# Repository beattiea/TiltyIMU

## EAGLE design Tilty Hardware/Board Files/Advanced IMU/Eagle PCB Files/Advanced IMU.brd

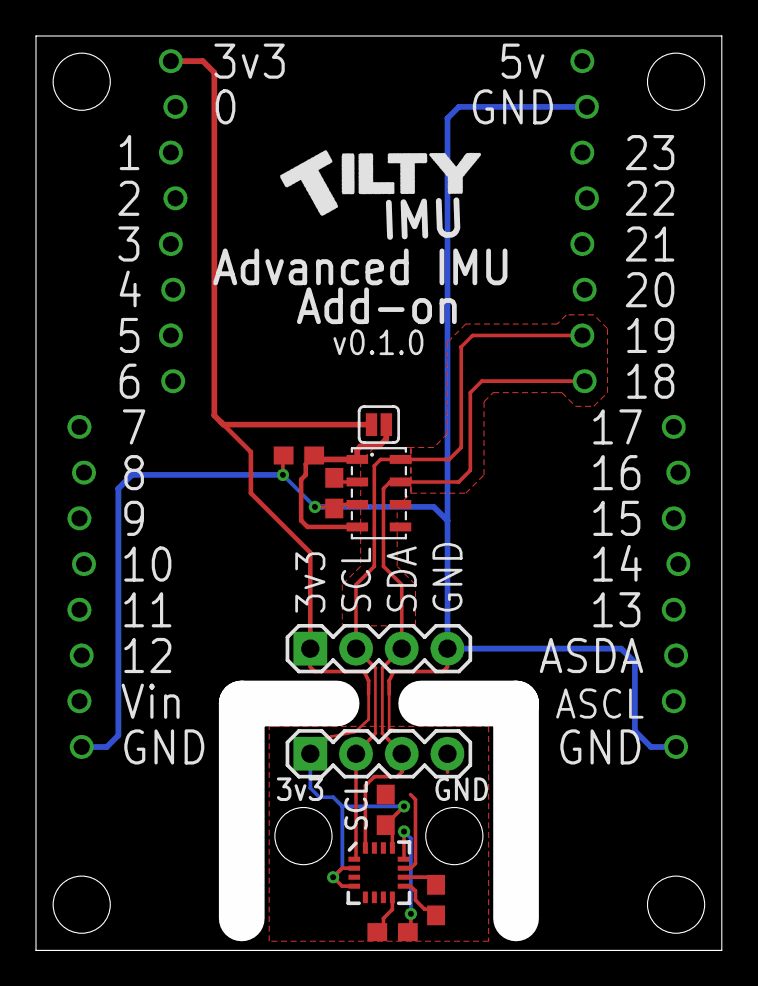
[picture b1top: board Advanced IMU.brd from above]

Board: 2 copper layers, 38.1 x 50.8 mm, 14 parts (0 on the bottom side), 9 nets.

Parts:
C6, C10, C12: 0.1uF; C0603
C7: 0.22uF; C0603
C8: 4.7uF; C0603
JP1, JP2, JP3, JP4: 8-PIN_HEADER; 8-PIN_RECEPTACLE_LOCK_NO-SS
JP5, JP6: 1X04
SJ1: SOLDERJUMPERNC; SJ_2S
U3: MPL3115A2LGA8; LGA8
U6: HMC5883LSMD; 16LPCC

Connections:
3V_SCL: JP4.P$7, JP5.2, JP6.2, U3.8, U6.1
3V_SDA: JP4.P$8, JP5.3, JP6.3, U3.7, U6.16
+3V3: C6.1, JP1.P$1, JP5.1, JP6.1, SJ1.2, U6.2, U6.4, U6.13
GND: C6.2, C8.2, C10.2, C12.1, JP2.P$8, JP3.P$8, JP4.P$2, JP5.4, JP6.4, U3.3, U6.9, U6.11
unnamed: C7.1, U6.8
unnamed: C7.2, U6.12
unnamed: C12.2, SJ1.1, U3.1, U3.4
unnamed: C8.1, U6.10
unnamed: C10.1, U3.2

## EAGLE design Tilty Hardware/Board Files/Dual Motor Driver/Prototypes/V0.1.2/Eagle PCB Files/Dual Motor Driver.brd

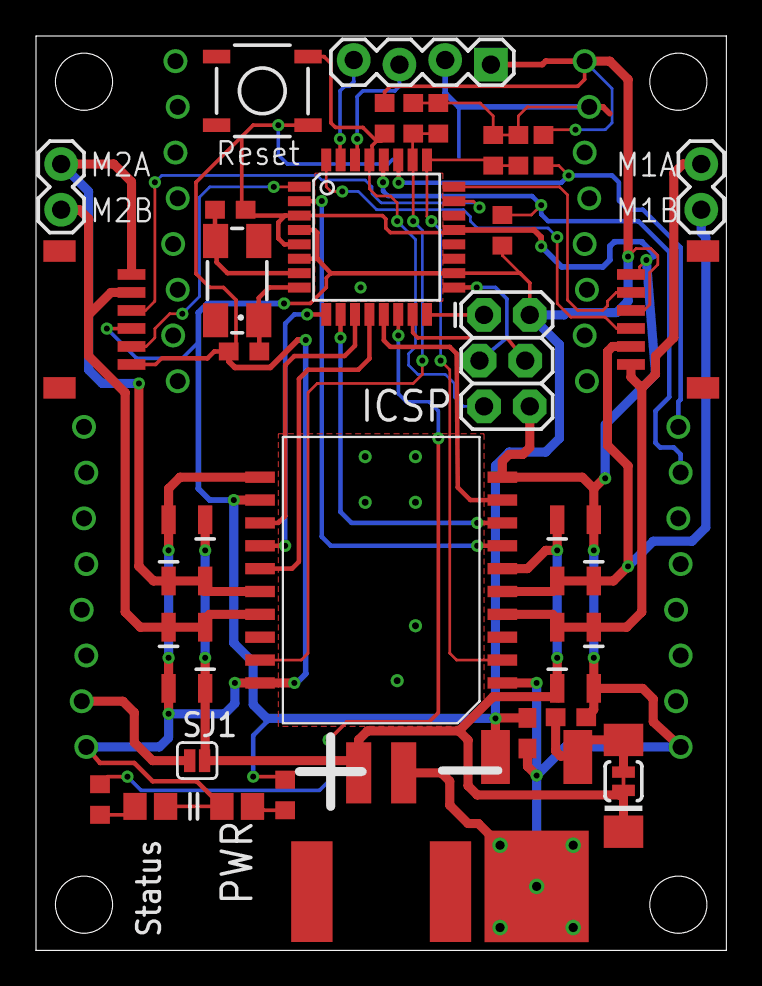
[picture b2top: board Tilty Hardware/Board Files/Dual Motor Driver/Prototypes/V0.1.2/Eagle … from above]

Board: 2 copper layers, 38.4 x 50.8 mm, 42 parts (0 on the bottom side), 34 nets.

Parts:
C2, C8: 22pF; C0603
C6: 4.7uF; C0603
C7: 0.1uF; C0603
D1, D2, D3, D4, D5, D6, D7, D8: SOD123
D9: DO214AA
D10, D11: LED-0805
J1: AVR_SPI_PRG_62X3_LOCK; 2X3_LOCK
JP1, JP2, JP3, JP4: 8-PIN_HEADER; 8-PIN_RECEPTACLE_LOCK_NO-SS
JP5, JP6: 6PIN-SH_RIGHT_ANGLE; 6PIN-SH_SERIES_RA
JP7: 2-POS_SMD_TERM_BLOCK; 2-POS_SMD_TERMINAL_BLOCK
JP8: 1X04_LOCK
JP9, JP10: 1X02
Q1: 16MHz; CTS406
R1: 10K; R0603
R2, R3, R4, R5: 1; R0603
R6, R7, R8, R9: R0603
S1: SWITCH-MOMENTARY-2SMD; TACTILE_SWITCH_SMD
SJ1: SOLDERJUMPERNC; SJ_2S
SJ2: SJ_2S-TRACE
U1: ATMEGA328P; TQFP32-08
U2: L298_BRIDGE_DRIVER; POWERSO20
U3: LM2931; TO263

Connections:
+5V: C6.1, J1.2, JP4.P$1, JP5.P$4, JP6.P$4, JP8.1, R1.2, R6.1, R7.2, R8.2, U1.4, U1.6, U1.18, U2.12, U3.P$3
+24V: D5.1, D6.1, D7.1, D8.1, D9.C, JP7.P$3, SJ1.2, SJ2.2, U2.6
ENC1A: JP6.P$3, U1.32
ENC1B: JP6.P$5, U1.24
ENC2A: JP5.P$3, U1.23
ENC2B: JP5.P$5, U1.1
GND: C2.1, C6.2, C7.2, C8.1, D1.2, D2.2, D3.2, D4.2, D10.2, D11.2, J1.6, JP2.P$1, JP3.P$1, JP4.P$2, JP5.P$6, JP6.P$6, JP7.P$4, JP8.2, R2.1, R3.1, R4.1, R5.1, S1.1, U1.3, U1.5, U1.21, U2.1, U2.10, U2.11, U2.20, U3.P$1
M1+: U1.2, U2.7
M1-: U1.13, U2.9
M1A: D1.1, D8.2, JP6.P$1, JP9.2, U2.4
M1B: D2.1, D7.2, JP6.P$2, JP9.1, U2.5
M2+: U1.11, U2.13
M2-: U1.12, U2.15
M2A: D3.1, D6.2, JP5.P$1, JP10.2, U2.16
M2B: D4.1, D5.2, JP5.P$2, JP10.1, U2.17
MISO: J1.1, U1.16
MOSI: J1.4, U1.15
unnamed: D10.1, R6.2
unnamed: D11.1, R9.2
unnamed: C7.1, D9.A, SJ2.1, U3.P$2
unnamed: R9.1, U1.14
unnamed: JP2.P$2, SJ1.1
unnamed: C8.2, Q1.3, U1.7
unnamed: C2.2, Q1.1, U1.8
PWM1: U1.10, U2.8
PWM2: U1.9, U2.14
RESET: J1.5, R1.1, S1.3, U1.29
RX: JP8.3, U1.30
SCK: J1.3, U1.17
SCL: JP3.P$7, R8.1, U1.28
SDA: JP3.P$8, R7.1, U1.27
SENSE_1: R2.2, R3.2, U1.25, U2.2
SENSE_2: R4.2, R5.2, U1.26, U2.19
TX: JP8.4, U1.31

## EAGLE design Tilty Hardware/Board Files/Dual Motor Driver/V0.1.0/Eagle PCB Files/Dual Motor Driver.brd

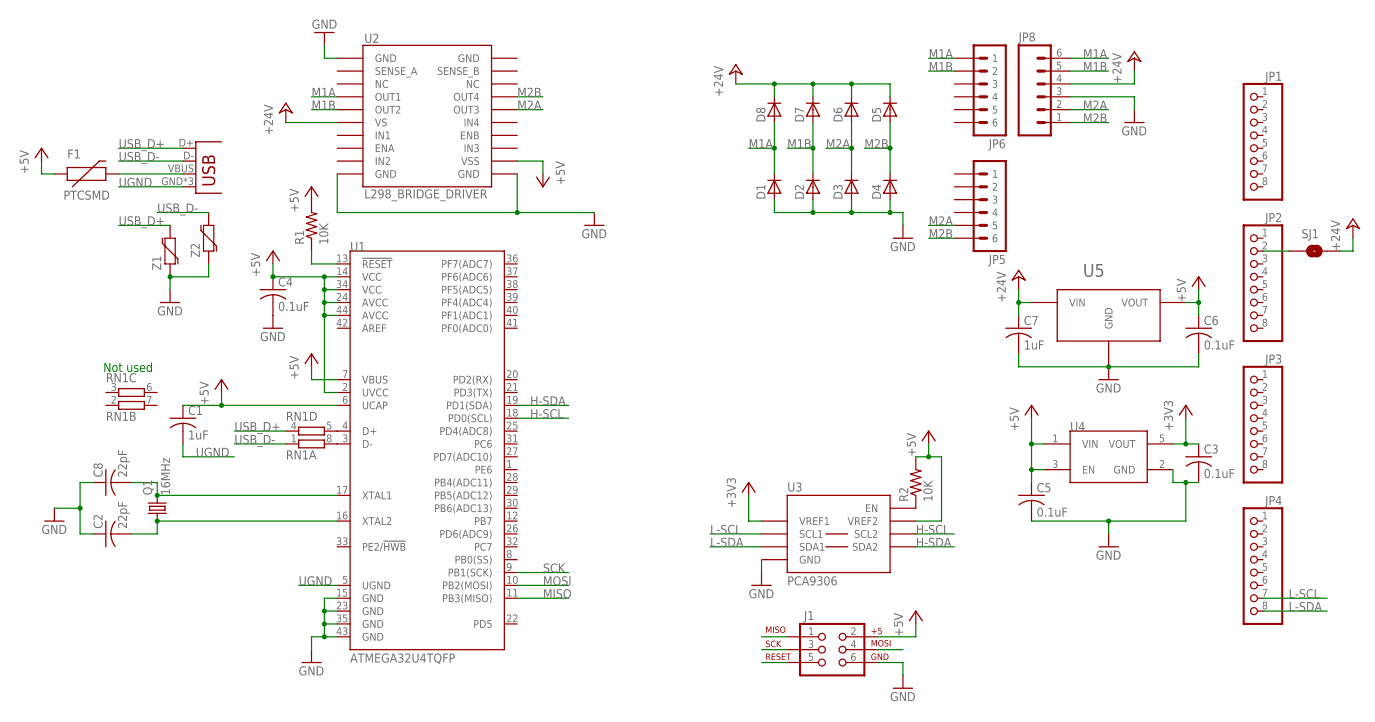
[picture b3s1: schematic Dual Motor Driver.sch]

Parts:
C1, C7: 1uF; C0603
C2, C8: 22pF; C0603
C3, C4, C5, C6: 0.1uF; C0603
D1, D2, D3, D4, D5, D6, D7, D8: D-SOD123; SOD123; PART# CDBW140-G
F1: PTCSMD; PTC-1206; PART# 0ZCJ0050FF2G
J1: AVR_SPI_PRG_6PTH; 2X3
JP1, JP2, JP3, JP4: PINHD-1X81X08_NO_SILK; 1X08_NO_SS
JP5, JP6: 6PIN-SH_RIGHT_ANGLE; 6PIN-SH_SERIES_RA; PART# SM06B-SRSS-TB(LF)(SN)
JP7: USB-MICROB
JP8: M063.5MM-6; SCREWTERMINAL-3.5MM-6
Q1: 16MHz; CTS406; PART# 406C35D16M00000
R1, R2: 10K; R0603
RN1: 4R-N0603-ARV; 0603-ARV
SJ1: SOLDERJUMPERNC; SJ_2S
U1: ATMEGA32U4TQFP; SPARKFUN-DIGITALIC_TQFP44
U2: L298_BRIDGE_DRIVER; POWERSO20
U3: PCA9306; SOIC-8; PART# PCA9306D,118
U4: TLV71333PDBVR; SOT23-5; PART# TLV71333PDBVR
U5: VOLTAGE-REGULATOR; SOT89; PART# L78L05ACUTR
Z1, Z2: VARISTOR-0603; 0603-RES; PART# CG0603MLC-05E

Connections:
+3V3: C3.1, U3.P$2 (VREF1), U4.5 (VOUT)
+5V: C1.1, C4.1, C5.1, C6.1, F1.1, J1.2, R1.2, R2.2, U1.2 (UVCC), U1.6 (UCAP), U1.7 (VBUS), U1.14 (VCC), U1.24 (AVCC), U1.34 (VCC), U1.44 (AVCC), U2.12 (VSS), U3.P$7 (VREF2), U4.1 (VIN), U4.3 (EN), U5.P$1 (VOUT)
+24V: C7.1, D5.1 (C), D6.1 (C), D7.1 (C), D8.1 (C), JP8.4, SJ1.2, U2.6 (VS), U5.P$3 (VIN)
GND: C2.1, C3.2, C4.2, C5.2, C6.2, C7.2, C8.1, D1.2 (A), D2.2 (A), D3.2 (A), D4.2 (A), J1.6, JP8.3, U1.15 (GND), U1.23 (GND), U1.35 (GND), U1.43 (GND), U2.1 (GND), U2.10 (GND), U2.11 (GND), U3.P$1 (GND), U4.2 (GND), U5.P$2 (GND), U5.P$4 (GND), Z1.1, Z2.1
H-SCL: U1.18 (PD0(SCL)), U3.P$6 (SCL2)
H-SDA: U1.19 (PD1(SDA)), U3.P$5 (SDA2)
L-SCL: JP4.7, U3.P$3 (SCL1)
L-SDA: JP4.8, U3.P$4 (SDA1)
M1A: D1.1 (C), D8.2 (A), JP6.P$1 (1), JP8.6, U2.4 (OUT1)
M1B: D2.1 (C), D7.2 (A), JP6.P$2 (2), JP8.5, U2.5 (OUT2)
M2A: D3.1 (C), D6.2 (A), JP5.P$5 (5), JP8.2, U2.16 (OUT3)
M2B: D4.1 (C), D5.2 (A), JP5.P$6 (6), JP8.1, U2.17 (OUT4)
MISO: J1.1, U1.11 (PB3(MISO))
MOSI: J1.4, U1.10 (PB2(MOSI))
unnamed: RN1.5 (2), U1.4 (D+)
unnamed: RN1.8 (2), U1.3 (D-)
unnamed: R2.1, U3.P$8 (EN)
unnamed: F1.2, JP7.VBUS
unnamed: JP2.2, SJ1.1
unnamed: C8.2, Q1.3 (2), U1.17 (XTAL1)
unnamed: C2.2, Q1.1, U1.16 (XTAL2)
RESET: J1.5, R1.1, U1.13 (!RESET)
SCK: J1.3, U1.9 (PB1(SCK))
UGND: C1.2, JP7.GND, JP7.MT1 (GND), JP7.MT2 (GND), U1.5 (UGND)
USB_D+: JP7.D+, RN1.4 (1), Z1.2
USB_D-: JP7.D-, RN1.1, Z2.2

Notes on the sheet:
Not used

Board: 2 copper layers, 38 parts (0 on the bottom side), 26 nets, no tracks yet.

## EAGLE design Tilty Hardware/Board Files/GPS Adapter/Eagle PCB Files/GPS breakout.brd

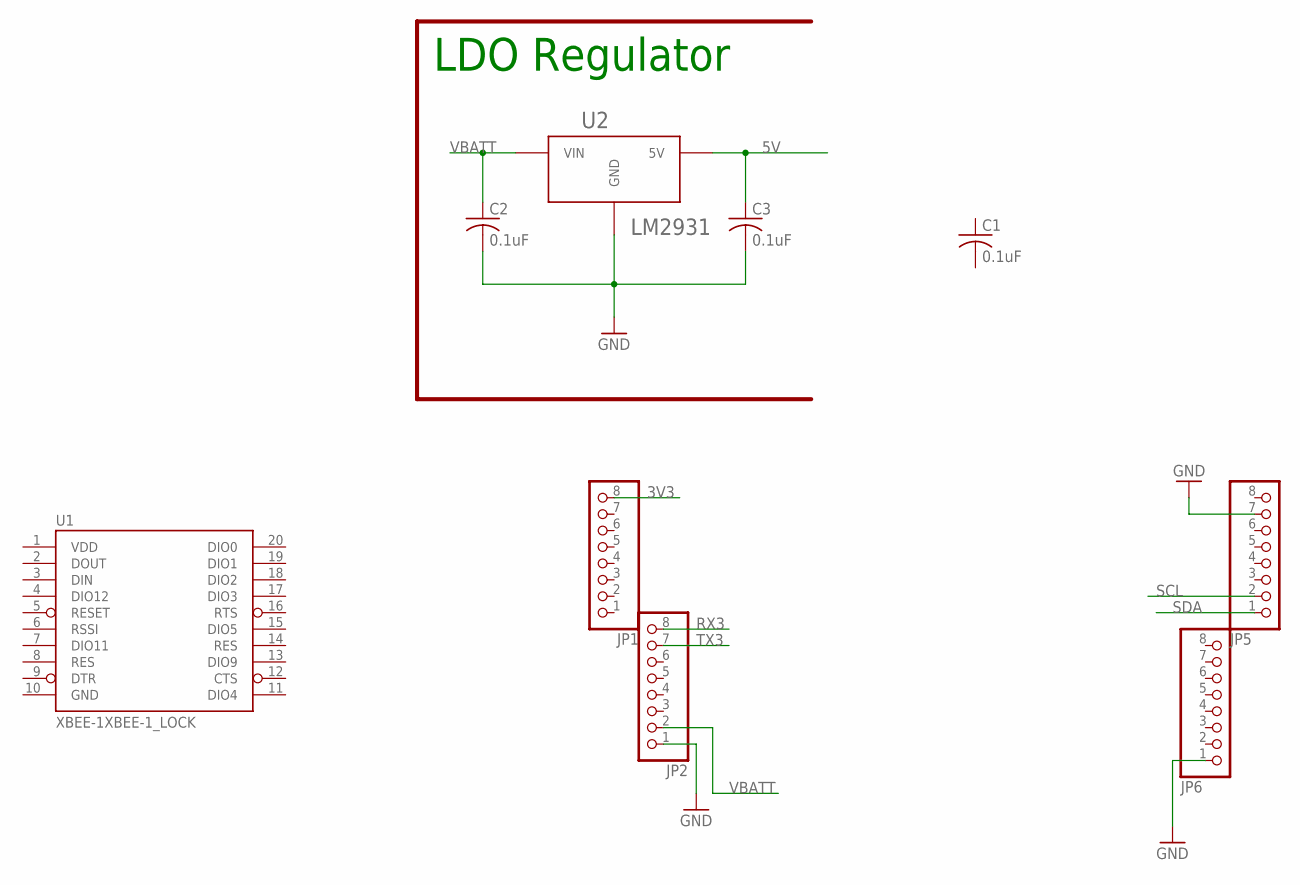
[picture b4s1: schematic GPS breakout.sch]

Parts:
C1, C2, C3: 0.1uF; C0603
JP1, JP2, JP5, JP6: PINHD-1X81X08_NO_SILK_LOCK; 1X08_NO_SS_LOCKING
U1: XBEE-1XBEE-1_LOCK; XBEE-1_LOCK
U2: LM2931; TO263

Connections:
3V3: JP1.8
5V: C3.1, U2.P$3 (5V)
GND: C2.2, C3.2, JP2.1, JP5.7, JP6.1, U1.10 (GND), U2.P$1 (GND)
RX3: JP2.8
SCL: JP5.2
SDA: JP5.1
TX3: JP2.7
VBATT: C2.1, JP2.2, U2.P$2 (VIN)
VDD: U1.1 (VDD)

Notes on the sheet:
LDO Regulator

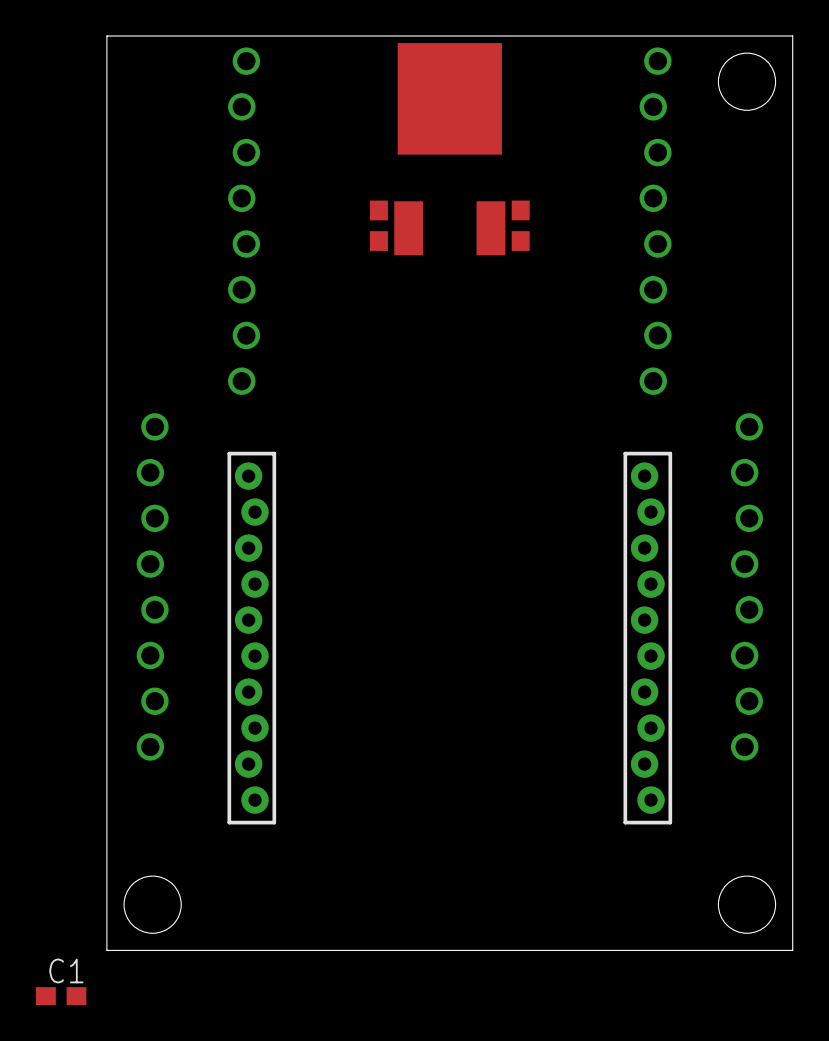
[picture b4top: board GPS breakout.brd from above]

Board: 2 copper layers, 38.1 x 50.8 mm, 9 parts (0 on the bottom side), 3 nets.

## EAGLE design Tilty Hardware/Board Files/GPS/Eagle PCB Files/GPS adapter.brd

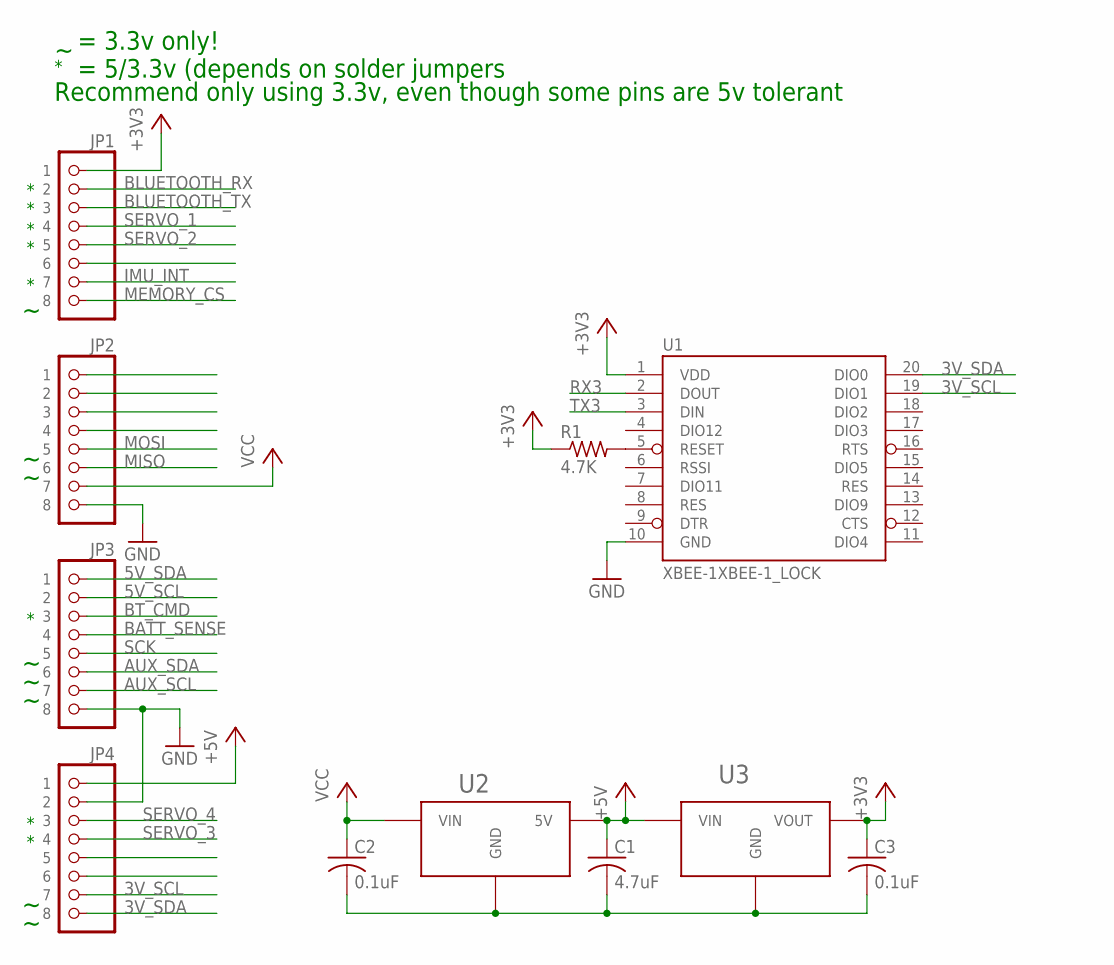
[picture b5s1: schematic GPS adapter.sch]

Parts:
C1: 4.7uF; C0603
C2, C3: 0.1uF; C0603
JP1, JP2, JP3, JP4: 8-PIN_HEADER; 8-PIN_RECEPTACLE_LOCK_NO-SS
R1: 4.7K; R0603
U1: XBEE-1XBEE-1_LOCK; XBEE-1_LOCK
U2: LM2931; TO263
U3: AP7313SOT23R; SOT23

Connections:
3V_SCL: JP4.P$7 (7), U1.19 (DIO1)
3V_SDA: JP4.P$8 (8), U1.20 (DIO0)
5V_SCL: JP3.P$2 (2)
5V_SDA: JP3.P$1 (1)
+3V3: C3.1, JP1.P$1 (1), R1.1, U1.1 (VDD), U3.P$2 (VOUT)
+5V: C1.1, JP4.P$1 (1), U2.P$3 (5V), U3.P$3 (VIN)
AUX_SCL: JP3.P$7 (7)
AUX_SDA: JP3.P$6 (6)
BATT_SENSE: JP3.P$4 (4)
BLUETOOTH_RX: JP1.P$2 (2)
BLUETOOTH_TX: JP1.P$3 (3)
BT_CMD: JP3.P$3 (3)
GND: JP2.P$8 (8), JP3.P$8 (8), JP4.P$2 (2), U1.10 (GND)
IMU_INT: JP1.P$7 (7)
MEMORY_CS: JP1.P$8 (8)
MISO: JP2.P$6 (6)
MOSI: JP2.P$5 (5)
unnamed: R1.2, U1.5 (RESET)
unnamed: C1.2, C2.2, C3.2, U2.P$1 (GND), U3.P$1 (GND)
RX3: U1.2 (DOUT)
SCK: JP3.P$5 (5)
SERVO_1: JP1.P$4 (4)
SERVO_2: JP1.P$5 (5)
SERVO_3: JP4.P$4 (4)
SERVO_4: JP4.P$3 (3)
TX3: U1.3 (DIN)
VCC: C2.1, JP2.P$7 (7), U2.P$2 (VIN)

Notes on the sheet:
= 3.3v only!
= 5/3.3v (depends on solder jumpers
Recommend only using 3.3v, even though some pins are 5v tolerant

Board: 2 copper layers, 11 parts (0 on the bottom side), 8 nets, no tracks yet.

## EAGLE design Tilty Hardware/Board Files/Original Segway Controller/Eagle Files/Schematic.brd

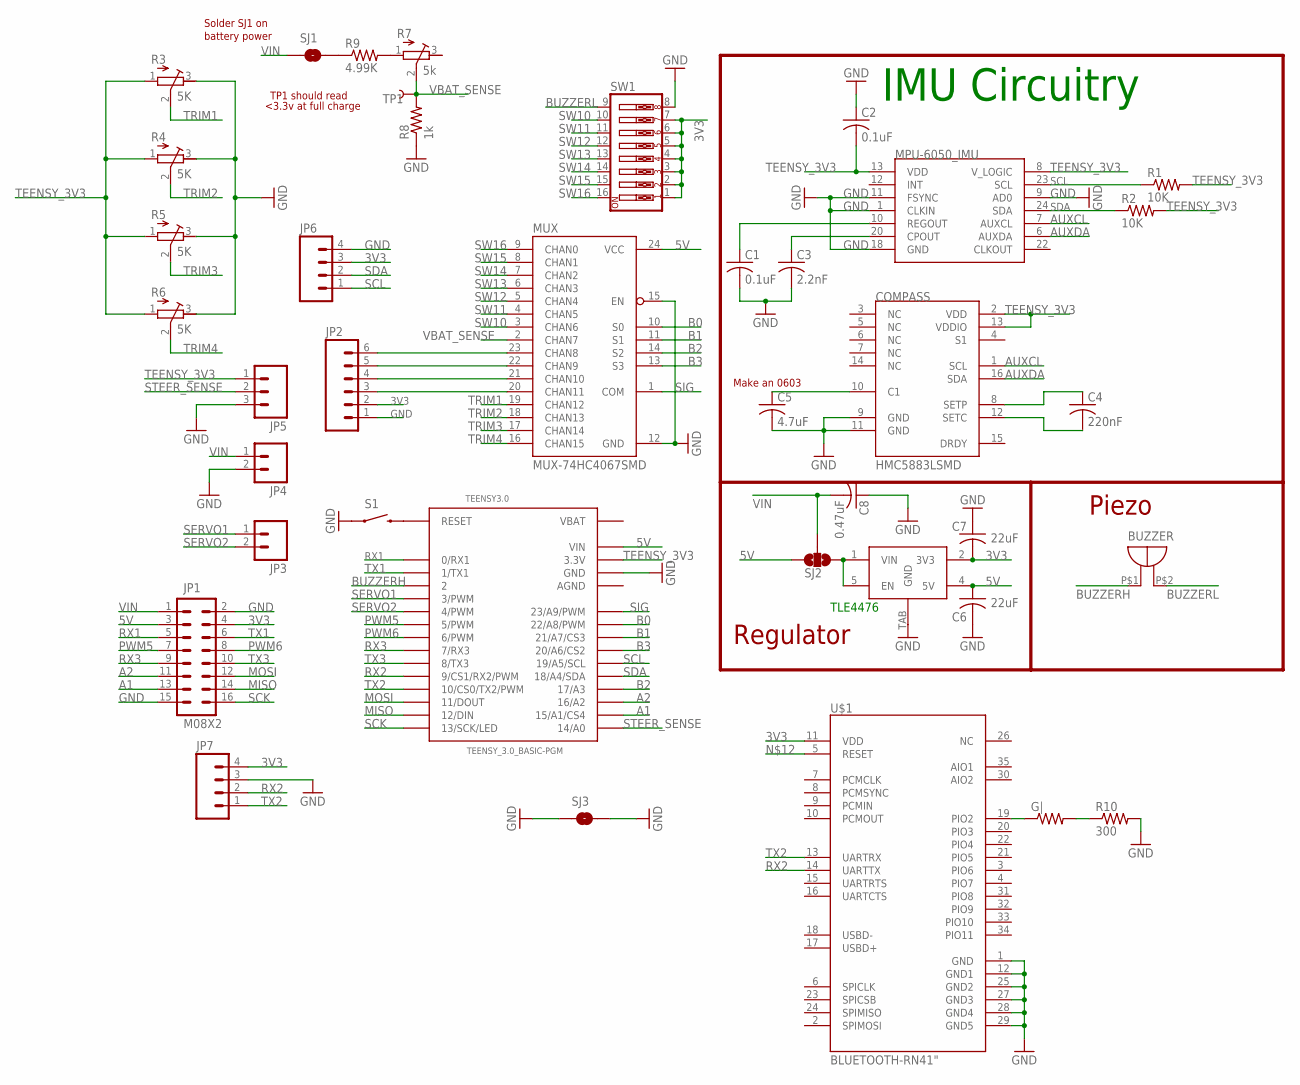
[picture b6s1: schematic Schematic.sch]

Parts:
BUZZER: PK-12N40PQ
C1: 0.1uF; C0603
C2: 0.1uF; C0603K
C3: 2.2nF; C0603
C4: 220nF; C0402
C5: 4.7uF; C0402
C6, C7: 22uF; C0805
C8: 0.47uF; C0805
COMPASS: HMC5883LSMD; 16LPCC
G|: R-US_R0805; R0805
IC1: TLE4467; TO252-5-11
JP1: M08X2; 2X8
JP2: M06SIP; 1X06
JP3, JP4: M023.5MM; SCREWTERMINAL-3.5MM-2
JP5: M03SCREW; SCREWTERMINAL-3.5MM-3
JP6, JP7: M04PTH; 1X04
MPU-6050_IMU: MPU-6050; QFN-24
MUX: MUX-74HC4067SMD; SSOP24
R1, R2: 10K; R0603
R3, R4, R5, R6: 5K; RTRIM3304W
R7: 5k; RTRIM3304W
R8: 1k; R0603
R9: 4.99K; R0603
R10: 300; R0603
S1: SWITCH-MOMENTARY-2SMD; TACTILE_SWITCH_SMD
SJ1, SJ3: SOLDERJUMPERNO; SJ_2S-NO
SJ2: SOLDERJUMPER_2WAYS; SJ_3
SW1: SW_DIP-8; DIPSWITCH-08
TEENSY3.0: TEENSY_3.0_BASIC-PGM
TP1: TEST-POINT3; PAD.03X.03
U$1: BLUETOOTH-RN41"; RN41

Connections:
3V3: C7.2, IC1.2 (3V3), JP1.4, JP2.2, JP6.3, JP7.4, SW1.1, SW1.2, SW1.3, SW1.4, SW1.5, SW1.6, SW1.7, U$1.11 (VDD)
5V: C6.1, IC1.4 (5V), JP1.3, MUX.24 (VCC), SJ2.3, TEENSY3.0.VIN
A1: JP1.13, TEENSY3.0.15/A1 (15/A1/CS4)
A2: JP1.11, TEENSY3.0.16/A2
AGND: TEENSY3.0.AGND
AUXCL: COMPASS.1 (SCL), MPU-6050_IMU.7 (AUXCL)
AUXDA: COMPASS.16 (SDA), MPU-6050_IMU.6 (AUXDA)
B0: MUX.10 (S0), TEENSY3.0.22/A8 (22/A8/PWM)
B1: MUX.11 (S1), TEENSY3.0.21/A7 (21/A7/CS3)
B2: MUX.14 (S2), TEENSY3.0.17/A3
B3: MUX.13 (S3), TEENSY3.0.20/A6 (20/A6/CS2)
BUZZERH: BUZZER.P$1 (+), TEENSY3.0.2
BUZZERL: BUZZER.P$2 (-), SW1.9
GND: C1.2, C2.1, C3.2, C5.2, C6.2, C7.1, C8.1, COMPASS.9 (GND), COMPASS.11 (GND), IC1.TAB (GND), JP1.2, JP1.15, JP2.1, JP4.2, JP5.3, JP6.4, JP7.3, MPU-6050_IMU.1 (CLKIN), MPU-6050_IMU.9 (AD0), MPU-6050_IMU.11 (FSYNC), MPU-6050_IMU.18 (GND), MUX.12 (GND), MUX.15 (EN), R3.3 (A), R4.3 (A), R5.3 (A), R6.3 (A), R8.1, R10.2, S1.1, SJ3.1, SJ3.2, SW1.8, TEENSY3.0.GND, TEENSY3.0.GND1 (GND), U$1.1 (GND), U$1.12 (GND1), U$1.25 (GND2), U$1.27 (GND3), U$1.28 (GND4), U$1.29 (GND5)
MISO: JP1.14, TEENSY3.0.12 (12/DIN)
MOSI: JP1.12, TEENSY3.0.11 (11/DOUT)
unnamed: C1.1, MPU-6050_IMU.10 (REGOUT)
unnamed: C3.1, MPU-6050_IMU.20 (CPOUT)
unnamed: R7.1 (E), R9.2
unnamed: R9.1, SJ1.2
unnamed: JP2.6, MUX.23 (CHAN8)
unnamed: JP2.5, MUX.22 (CHAN9)
unnamed: C4.1, COMPASS.8 (SETP)
unnamed: C4.2, COMPASS.12 (SETC)
unnamed: C5.1, COMPASS.10 (C1)
unnamed: JP2.4, MUX.21 (CHAN10)
unnamed: JP2.3, MUX.20 (CHAN11)
unnamed: S1.3 (2), TEENSY3.0.RESET, U$1.5 (RESET)
unnamed: G|.1, U$1.19 (PIO2)
unnamed: G|.2, R10.1
PWM5: JP1.7, TEENSY3.0.5 (5/PWM)
PWM6: JP1.8, TEENSY3.0.6 (6/PWM)
REG_IN: IC1.1 (VIN), IC1.5 (EN), SJ2.1
RX1: JP1.5, TEENSY3.0.0 (0/RX1)
RX2: JP7.2, TEENSY3.0.9 (9/CS1/RX2/PWM), U$1.14 (UARTTX)
RX3: JP1.9, TEENSY3.0.7 (7/RX3)
SCK: JP1.16, TEENSY3.0.13 (13/SCK/LED)
SCL: JP6.1, MPU-6050_IMU.23 (SCL), R1.1, TEENSY3.0.19/A5 (19/A5/SCL)
SDA: JP6.2, MPU-6050_IMU.24 (SDA), R2.1, TEENSY3.0.18/A4 (18/A4/SDA)
SERVO1: JP3.1, TEENSY3.0.3 (3/PWM)
SERVO2: JP3.2, TEENSY3.0.4 (4/PWM)
SIG: MUX.1 (COM), TEENSY3.0.23/A9 (23/A9/PWM)
STEER_SENSE: JP5.2, TEENSY3.0.14/A0
SW10: MUX.3 (CHAN6), SW1.10
SW11: MUX.4 (CHAN5), SW1.11
SW12: MUX.5 (CHAN4), SW1.12
SW13: MUX.6 (CHAN3), SW1.13
SW14: MUX.7 (CHAN2), SW1.14
SW15: MUX.8 (CHAN1), SW1.15
SW16: MUX.9 (CHAN0), SW1.16
TEENSY_3V3: C2.2, COMPASS.2 (VDD), COMPASS.13 (VDDIO), JP5.1, MPU-6050_IMU.8 (V_LOGIC), MPU-6050_IMU.13 (VDD), R1.2, R2.2, R3.1 (E), R4.1 (E), R5.1 (E), R6.1 (E), TEENSY3.0.3.3V, TEENSY3.0.3.3V1 (3.3V)
TRIM1: MUX.19 (CHAN12), R3.2 (S)
TRIM2: MUX.18 (CHAN13), R4.2 (S)
TRIM3: MUX.17 (CHAN14), R5.2 (S)
TRIM4: MUX.16 (CHAN15), R6.2 (S)
TX1: JP1.6, TEENSY3.0.1 (1/TX1)
TX2: JP7.1, TEENSY3.0.10 (10/CS0/TX2/PWM), U$1.13 (UARTRX)
TX3: JP1.10, TEENSY3.0.8 (8/TX3)
VBAT_SENSE: MUX.2 (CHAN7), R7.2 (S), R8.2, TP1.P$1
VIN: C8.2, JP1.1, JP4.1, SJ1.1, SJ2.2, TEENSY3.0.VBAT

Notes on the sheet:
IMU Circuitry
Regulator
Piezo
TP1 should read
<3.3v at full charge
Solder SJ1 on
battery power
Make an 0603
TLE4476

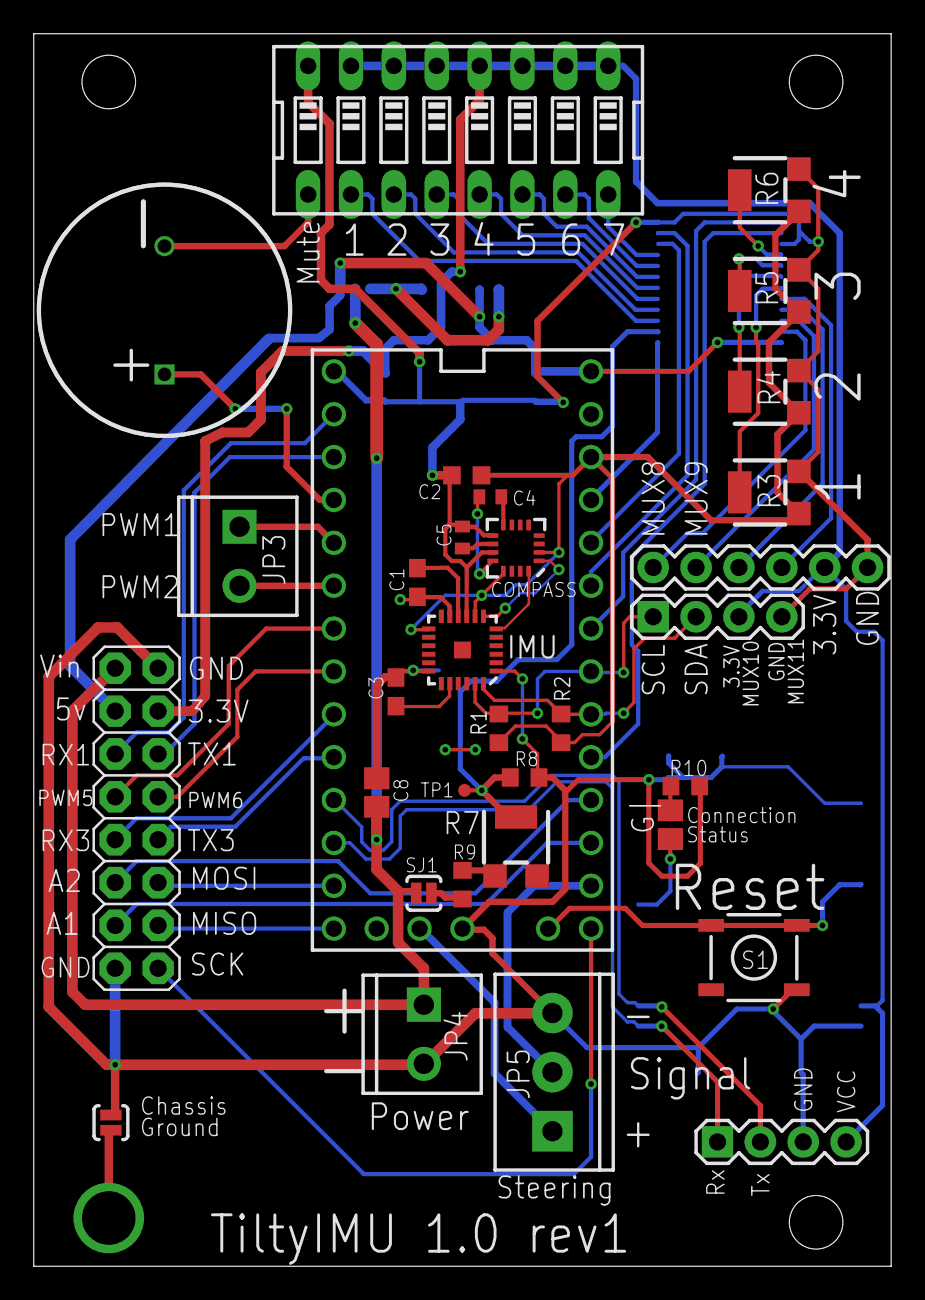
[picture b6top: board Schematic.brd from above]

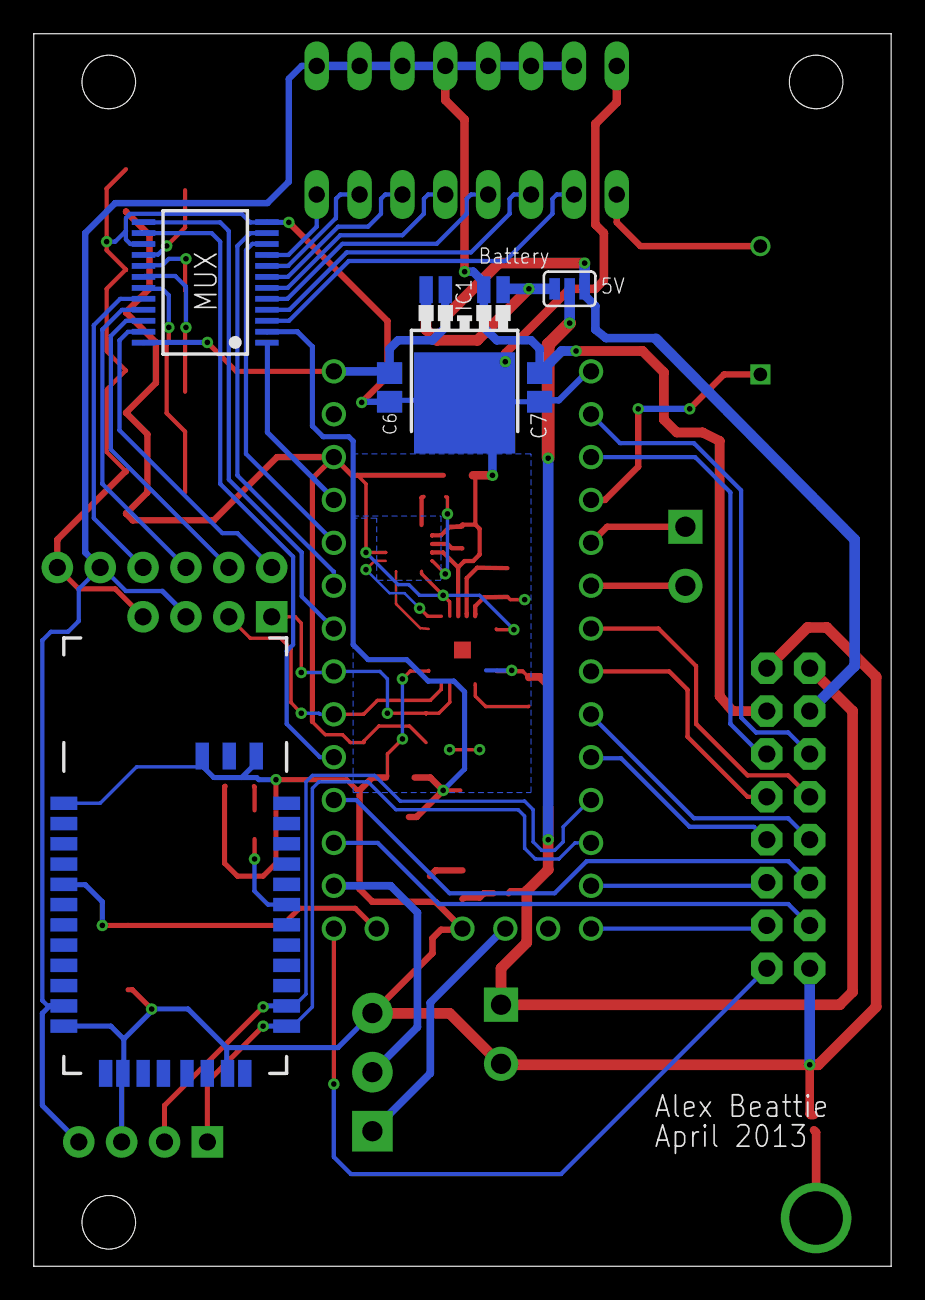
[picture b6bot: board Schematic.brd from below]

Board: 2 copper layers, 50.8 x 73.0 mm, 39 parts (6 on the bottom side), 59 nets.

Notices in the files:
parts and their libraries:
SparkFun-Sensors: Licensing: CC v3.0 Share-Alike You are welcome to use this library for commercial purposes.
